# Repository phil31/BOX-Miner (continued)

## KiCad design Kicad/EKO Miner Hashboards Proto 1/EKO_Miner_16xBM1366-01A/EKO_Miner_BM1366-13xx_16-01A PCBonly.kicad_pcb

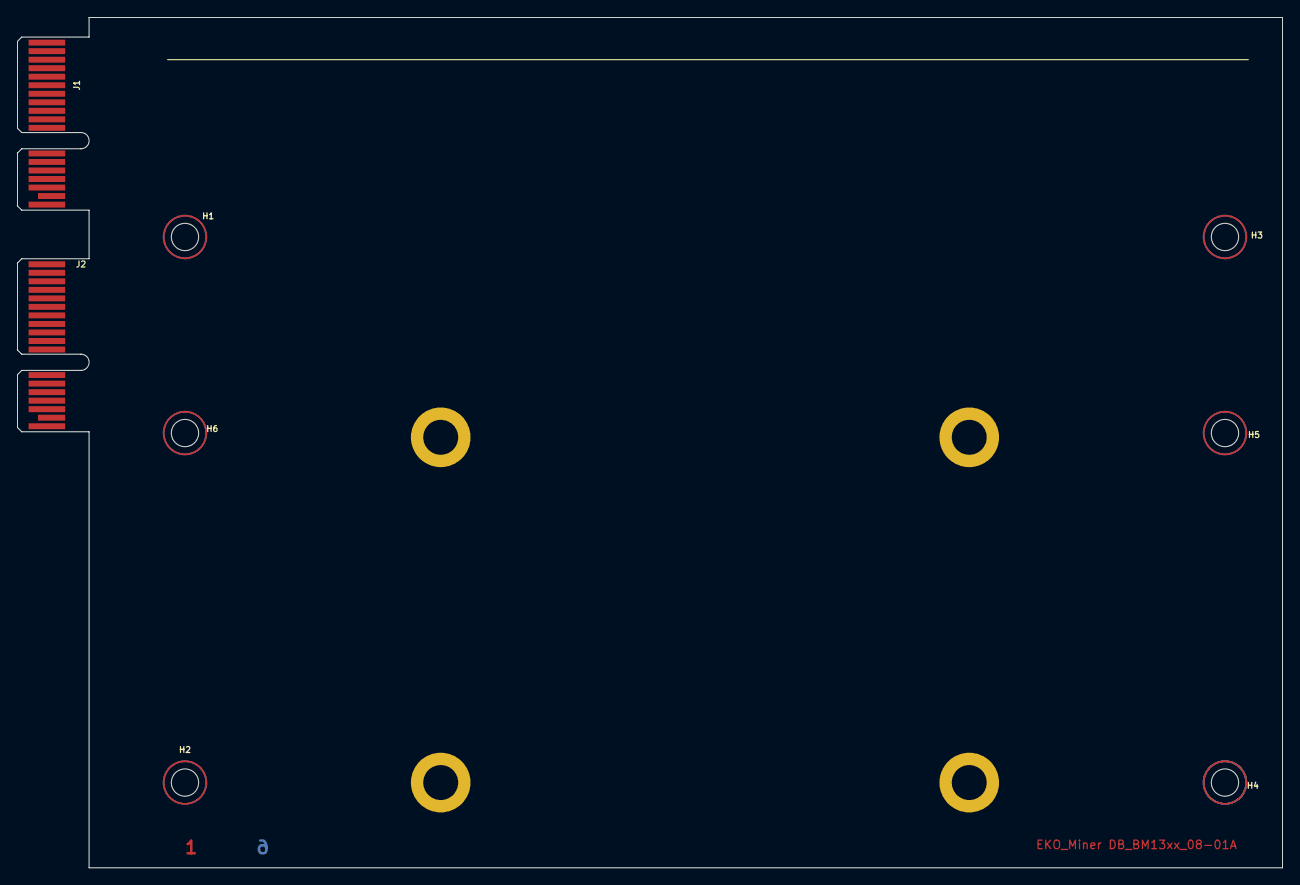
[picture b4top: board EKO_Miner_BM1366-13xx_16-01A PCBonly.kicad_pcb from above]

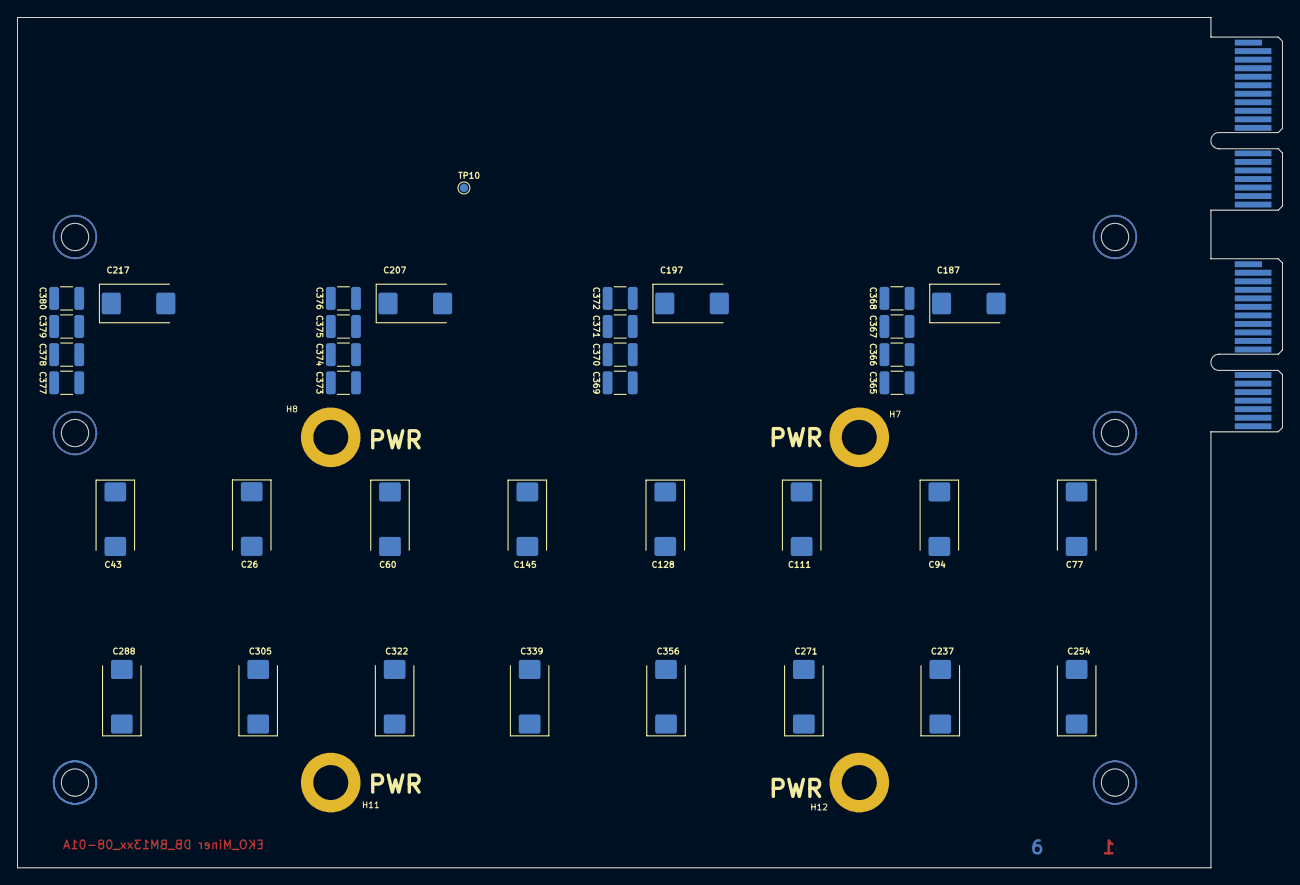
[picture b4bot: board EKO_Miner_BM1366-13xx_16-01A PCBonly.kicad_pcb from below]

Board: 6 copper layers, 148.4 x 99.8 mm, 49 parts (41 on the bottom side), 3 nets.

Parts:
C26, C43, C60, C77, C94, C111, C128, C145, C187, C197, C207, C217, C237, C254, C271, C288, C305, C322, C339, C356: 330uF; CP_EIA-7343-31_Kemet-D_Pad2.25x2.55mm_HandSolder
C365, C366, C367, C368, C369, C370, C371, C372, C373, C374, C375, C376, C377, C378, C379, C380: 100uF; C_1210_3225Metric
H1, H2, H3, H4, H5, H6: MountingHole; MountingHole_3.2mm_M3_ISO7380
H7, H8, H11, H12: MountingHole_Pad; SMTSO-M3-3ET
J1, J2: 10018784-10210TLF; BUS_PCIexpress_x1
TP10: TestPoint; TestPoint_Pad_D1.0mm

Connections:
+12V_PWR: J1.B1, J1.B2, J1.B3, J1.B4, J1.B5, J1.B6, J1.B7, J1.B8, J1.B9, J1.B10, J1.B11, J1.B12, J1.B13, J1.B14, J1.B15, J1.B16, J1.B17, J1.B18, J2.B1, J2.B2, J2.B3, J2.B4, J2.B5, J2.B6, J2.B7, J2.B8, J2.B9, J2.B10, J2.B11
GND: C26.2, C43.2, C60.2, C77.2, C94.2, C111.2, C128.2, C145.2, C187.2, C197.2, C207.2, C217.2, C237.2, C254.2, C271.2, C288.2, C305.2, C322.2, C339.2, C356.2, C365.2, C366.2, C367.2, C368.2, C369.2, C370.2, C371.2, C372.2, C373.2, C374.2, C375.2, C376.2, C377.2, C378.2, C379.2, C380.2, J1.A1, J1.A2, J1.A3, J1.A4, J1.A5, J1.A6, J1.A7, J1.A8, J1.A9, J1.A10, J1.A11, J1.A12, J1.A13, J1.A14, J1.A15, J1.A16, J1.A17, J1.A18, J2.A1, J2.A2, J2.A3, J2.A4, J2.A5, J2.A6, J2.A7, J2.A8, J2.A9, J2.A10, J2.A11
VPWR_ASIC: C26.1, C43.1, C60.1, C77.1, C94.1, C111.1, C128.1, C145.1, C187.1, C197.1, C207.1, C217.1, C237.1, C254.1, C271.1, C288.1, C305.1, C322.1, C339.1, C356.1, C365.1, C366.1, C367.1, C368.1, C369.1, C370.1, C371.1, C372.1, C373.1, C374.1, C375.1, C376.1, C377.1, C378.1, C379.1, C380.1, H7.1, H8.1, H11.1, H12.1

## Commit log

2024-12-08 first release
2024-12-09 update Hashboard 1368
